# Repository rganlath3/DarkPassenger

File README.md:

# Dark Passenger

A modular payload for use as a ROS learning platform. Each floor of the chassis delivers different capabilities. The initial design is mounted on a differential drive roomba with plans to expand to treaded or quad-coptor platforms.

<!-- ABOUT THE PROJECT -->
## About The Project
The idea was to reuse a cheap roomba to create a platform for learning ROS2 and sensor integration. The end goal is to have a project incorporate aluminum extrusion chassis, working with acrylic, ESP32-S3, KiCAD PCB Development, stepper motors, thermal camera, depth camera, LIDAR, slip rings, DC motor controllers, encoders, 3D printing, INS sensor fusion, relays, GPS, SLAM, NAV2 (navigation stack) and power distribution.

### Design Tools & Requirements

#### Software Requirements
- VS Code (Programming IDE)
- Autodesk Fusion360 (Free CAD Software)
- KiCAD 9.0 (Open Source PCB Design Software)
- Ultimaker Cura (Free 3D Slicing Software)

#### Hardware Requirements
- Raspberry Pi 5
- 32GB+ SD Card
- 1x Dewalt 20VDC 2Ah Battery

## Hardware Development

### Bill of Materials
Coming Soon

### Hardware Used
#### Chassis
* 2020 T Slot Aluminum Extrusion
* 2020 2-Way Corner Brackets
* 2020 3-Way Corner Brackets
* M5 T Nuts and Screws
* 8x10 Black Translucent Acrylic Sheets 1/8" thick.

#### Floor 1
* 2x DROK Step Down Voltage Regulator
* 2x 3V Relay Modules
* 1x Custom Power Distribution PCB
* 1x Custom ESP3 GPIO PCB
* 1x ESP32-S3-N8R2
* 1x COB LED Strip Yellow
* 1x COB LED Strip Red
* 1x Cytron Dual Channel 10A DC Motor Driver
* 1x Quick Disconnect 12Pin Connector
* 1x MPU9250 IMU
* 1x GY-NEO6MV2 GPS Module

#### Floor 2
* 2x Acer USB Powered Hub
* 1x Raspberry Pi 5 (SBC)
* 1x Respeaker Microphone Array
* 1x ZED Stereo Labs Depth Camera

#### Floor 3
* 1x A1M8 RPLIDAR LIDAR Sensor
* 1x GPS Antenna

#### Floor 4
* 1x Custom ESP3 GPIO PCB
* 1x ESP32-S3-N8R2
* 1x Taidacent Hollow Slip Ring (Maybe 2x)
* 1x 5mm Flange Coupler
* 2x TMC2209 V1.3 Stepper Motor Driver
* 2x NEMA 17 Stepper (2A, 59Ncm), 48mm
* 1x Chameleon Camera Teledyne CM3-U3-13S2C-CS
* 3x 3V Relay Modules
* 1x MDD3A Dual Channel 3A DC Motor Driver
* 1x NERF Gun Gearbox
* 1x Laser Diode, 5V 1mA
* 1x COB LED Strip Yellow
* 1x 5V or 12V Cooling Fan

#### Misc
* Various Capacitors, Resistors, SMD LEDs, JST Connectors, Wire Crimps, etc.
* Various stranded wire lengths and colors: 16AWG, 22AWG.
* 1x 2.1mm DC Barrel Jacks Pair (Power Input)
* 1x SPST 20A Heavy Duty Toggle Switch (Projector Power and Pi Power)
* 2x SPST 5A Mini Toggle Switch (LED Power)
* 3D Printer: Creality CR-10SProV2

### Internal Block Diagram

### Electrical Interconnect Diagram
[Electrical Interconnect Diagram](/Hardware_Development/DrawIO/DarkPassengerElectricalInterconnect.pdf)

### PCBs
#### Power Distribution PCB

This PCB is used to stack 2x DC-DC converters below and a voltage cutoff board on the top. This PCB distributes power from battery inputs to get converted to 12V and 5V. It interfaces with the following components:

- Up to 2x 2Ah Dewalt Batteries
- Voltage Cutoff CCA (TBD)
- 20VDC to 5VDC Converter (TBD)
- 20VDC to 12VDC Converter (TBD)
- 3x Powered USB Ports
- Spare I2C

#### Base MCU PCB

This PCB is used to interface an ESP32-S3 with the following components:

- GPS Module (GY-NEO6mV2)
- MPU9250 IMU
- Spare I2C
- 2x Toggle Switches
- Neopixel Strip
- 2x Spare GPIOs
- External Reset
- 2x Channel Motor Driver (MDD10A)
- Battery Scaled Input
- Motor Encoders
- FWD LED Relay
- AFT LED Relay
- 5V Distribution

#### Turret MCU PCB

This PCB is used to interface an ESP32-S3 with the following components:

- GPS Module (GY-NEO6mV2)
- MPU9250 IMU
- Spare I2C
- Neopixel Strip
- External Reset
- 2x Channel Motor Driver (MDD3A)
- 2x NEMA17 Stepper Motors
- 2x TMC2209 Stepper Driver
- Laser Relay
- Turret LED Relay
- Cooling Fan Relay
- 5V Distribution
- 12V Distribution

### Power Budget and Power Draw
TBD

## Software Development
TBD
<!-- GETTING STARTED -->
## Getting Started

TBD
### Prerequisites
TBD

### Installation

TBD

### Common Issues

TBD

## Assets

TBD

<!-- ROADMAP -->
## Roadmap
- [] TBD

<p align="right">(<a href="#readme-top">back to top</a>)</p>

<!-- CONTRIBUTING -->
## Contributing & Donations

Any donation helps to support parts for future open source projects!
[Buy Me a Coffee ☕](https://www.buymeacoffee.com/rganlath)

Contributions are what make the open source community such an amazing place to learn, inspire, and create. Any contributions you make are **greatly appreciated**.

If you have a suggestion that would make this better, please fork the repo and create a pull request. You can also simply open an issue with the tag "enhancement".
Don't forget to give the project a star! Thanks again!

<p align="right">(<a href="#readme-top">back to top</a>)</p>

<!-- LICENSE -->
## License
The contents of this project itself is licensed under CERN-OHL-S-2.0 and the underlying source code is licensed under GNU GPLv3. Both of these licenses require attribution.

<p align="right">(<a href="#readme-top">back to top</a>)</p>

<!-- CONTACT -->
## Contact

Ranil Ganlath - ranil.ganlath@gmail.com

Project Link: TBD

<p align="right">(<a href="#readme-top">back to top</a>)</p>

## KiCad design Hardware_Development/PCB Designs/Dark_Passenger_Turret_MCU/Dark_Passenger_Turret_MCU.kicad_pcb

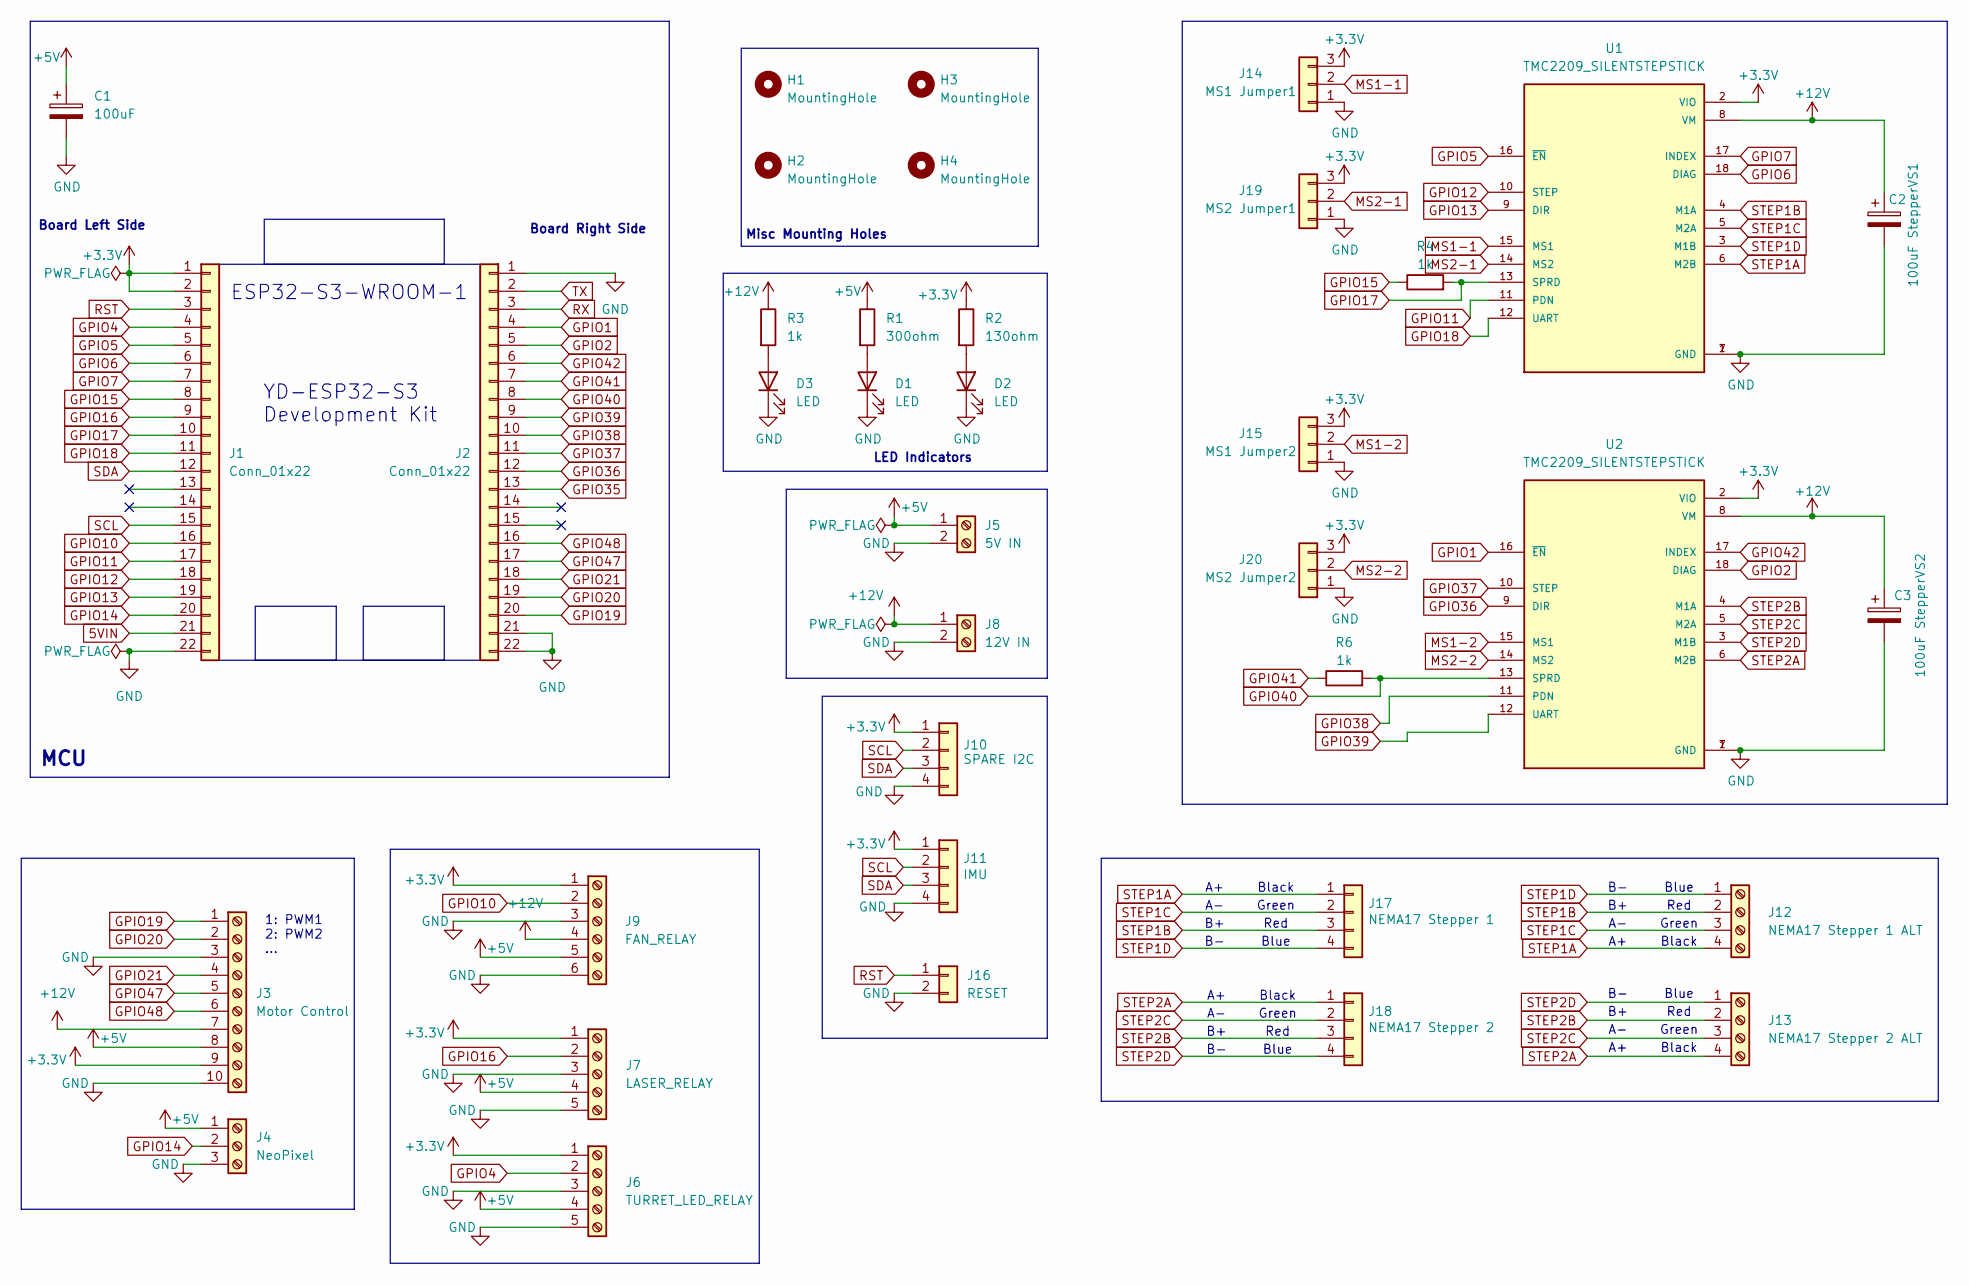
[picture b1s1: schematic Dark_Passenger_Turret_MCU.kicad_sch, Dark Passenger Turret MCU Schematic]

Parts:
C1: 100uF; CP_Radial_D10.0mm_P5.00mm
C2: 100uF StepperVS1; CP_Radial_D8.0mm_P5.00mm
C3: 100uF StepperVS2; CP_Radial_D8.0mm_P5.00mm
D1, D2, D3: LED; LED_1206_3216Metric_Pad1.42x1.75mm_HandSolder
H1, H2, H3, H4: MountingHole; MountingHole_3mm
J1, J2: Conn_01x22; PinSocket_1x22_P2.54mm_Vertical
J3: Motor Control; TerminalBlock_Phoenix_MPT-0,5-10-2.54_1x10_P2.54mm_Horizont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
J4: NeoPixel; TerminalBlock_Phoenix_MPT-0,5-3-2.54_1x03_P2.54mm_Horizontal
J5: 5V IN; TerminalBlock_Phoenix_MKDS-1,5-2_1x02_P5.00mm_Horizontal
J6: TURRET_LED_RELAY; TerminalBlock_Phoenix_MPT-0,5-5-2.54_1x05_P2.54mm_Horizontal
J7: LASER_RELAY; TerminalBlock_Phoenix_MPT-0,5-5-2.54_1x05_P2.54mm_Horizontal
J8: 12V IN; TerminalBlock_Phoenix_MKDS-1,5-2_1x02_P5.00mm_Horizontal
J9: FAN_RELAY; TerminalBlock_Phoenix_MPT-0,5-6-2.54_1x06_P2.54mm_Horizontal
J10: SPARE I2C; PinSocket_1x04_P2.54mm_Vertical
J11: IMU; PinSocket_1x04_P2.54mm_Vertical
J12: NEMA17 Stepper 1 ALT; TerminalBlock_Phoenix_MPT-0,5-4-2.54_1x04_P2.54mm_Horizontal
J13: NEMA17 Stepper 2 ALT; TerminalBlock_Phoenix_MPT-0,5-4-2.54_1x04_P2.54mm_Horizontal
J14: MS1 Jumper1; PinHeader_1x03_P2.54mm_Vertical
J15: MS1 Jumper2; PinHeader_1x03_P2.54mm_Vertical
J16: RESET; PinSocket_1x02_P2.54mm_Vertical
J17: NEMA17 Stepper 1; PinSocket_1x04_P2.54mm_Vertical
J18: NEMA17 Stepper 2; PinSocket_1x04_P2.54mm_Vertical
J19: MS2 Jumper1; PinHeader_1x03_P2.54mm_Vertical
J20: MS2 Jumper2; PinHeader_1x03_P2.54mm_Vertical
R1: 300ohm; R_1206_3216Metric_Pad1.30x1.75mm_HandSolder
R2: 130ohm; R_1206_3216Metric_Pad1.30x1.75mm_HandSolder
R3, R4, R6: 1k; R_1206_3216Metric_Pad1.30x1.75mm_HandSolder
U1, U2: TMC2209_SILENTSTEPSTICK; MODULE_TMC2209_SILENTSTEPSTICK; PARTREV 1.20

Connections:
5VIN: J1.21
+3.3V: J1.1, J1.2, J3.9, J6.1, J7.1, J9.1, J10.1, J11.1, J14.3, J15.3, J19.3, J20.3, R2.1, U1.2 (VIO), U2.2 (VIO)
+5V: C1.1, J3.8, J4.1, J5.1, J6.4, J7.4, J9.5, R1.1
+12V: C2.1, C3.1, J3.7, J8.1, J9.4, R3.1, U1.8 (VM), U2.8 (VM)
GND: C1.2, C2.2, C3.2, D1.1 (K), D2.1 (K), D3.1 (K), J1.22, J2.1, J2.21, J2.22, J3.3, J3.10, J4.3, J5.2, J6.3, J6.5, J7.3, J7.5, J8.2, J9.3, J9.6, J10.4, J11.4, J14.1, J15.1, J16.2, J19.1, J20.1, U1.1 (GND), U1.7 (GND), U2.1 (GND), U2.7 (GND)
GPIO1: J2.4, U2.16 (~EN)
GPIO2: J2.5, U2.18 (DIAG)
GPIO4: J1.4, J6.2
GPIO5: J1.5, U1.16 (~EN)
GPIO6: J1.6, U1.18 (DIAG)
GPIO7: J1.7, U1.17 (INDEX)
GPIO10: J1.16, J9.2
GPIO11: J1.17, U1.11 (PDN)
GPIO12: J1.18, U1.10 (STEP)
GPIO13: J1.19, U1.9 (DIR)
GPIO14: J1.20, J4.2
GPIO15: J1.8, R4.1
GPIO16: J1.9, J7.2
GPIO17: J1.10, R4.2, U1.13 (SPRD)
GPIO18: J1.11, U1.12 (UART)
GPIO19: J2.20, J3.1
GPIO20: J2.19, J3.2
GPIO21: J2.18, J3.4
GPIO35: J2.13
GPIO36: J2.12, U2.9 (DIR)
GPIO37: J2.11, U2.10 (STEP)
GPIO38: J2.10, U2.11 (PDN)
GPIO39: J2.9, U2.12 (UART)
GPIO40: J2.8, R6.2, U2.13 (SPRD)
GPIO41: J2.7, R6.1
GPIO42: J2.6, U2.17 (INDEX)
GPIO47: J2.17, J3.5
GPIO48: J2.16, J3.6
MS1-1: J14.2, U1.15 (MS1)
MS1-2: J15.2, U2.15 (MS1)
MS2-1: J19.2, U1.14 (MS2)
MS2-2: J20.2, U2.14 (MS2)
unnamed: D1.2 (A), R1.2
unnamed: D2.2 (A), R2.2
unnamed: D3.2 (A), R3.2
RST: J1.3, J16.1
RX: J2.3
SCL: J1.15, J10.2, J11.2
SDA: J1.12, J10.3, J11.3
STEP1A: J12.4, J17.1, U1.6 (M2B)
STEP1B: J12.2, J17.3, U1.4 (M1A)
STEP1C: J12.3, J17.2, U1.5 (M2A)
STEP1D: J12.1, J17.4, U1.3 (M1B)
STEP2A: J13.4, J18.1, U2.6 (M2B)
STEP2B: J13.2, J18.3, U2.4 (M1A)
STEP2C: J13.3, J18.2, U2.5 (M2A)
STEP2D: J13.1, J18.4, U2.3 (M1B)
TX: J2.2

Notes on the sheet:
Red
Blue
Misc Mounting Holes
ESP32-S3-WROOM-1
Black
Board Right Side
MCU
LED Indicators
Green
Board Left Side
1: PWM1 2: PWM2 ...
YD-ESP32-S3 Development Kit

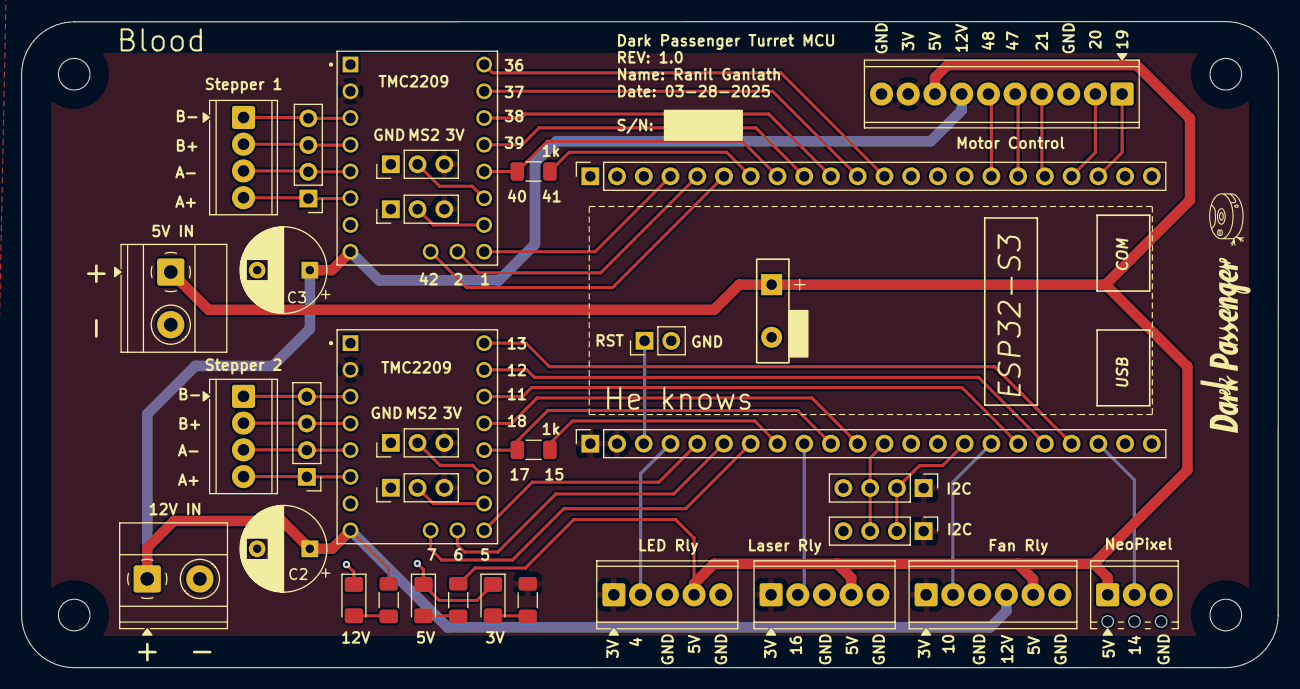
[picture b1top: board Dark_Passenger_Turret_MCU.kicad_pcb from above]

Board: 2 copper layers, 119.4 x 61.4 mm, 37 parts (0 on the bottom side), 49 nets.

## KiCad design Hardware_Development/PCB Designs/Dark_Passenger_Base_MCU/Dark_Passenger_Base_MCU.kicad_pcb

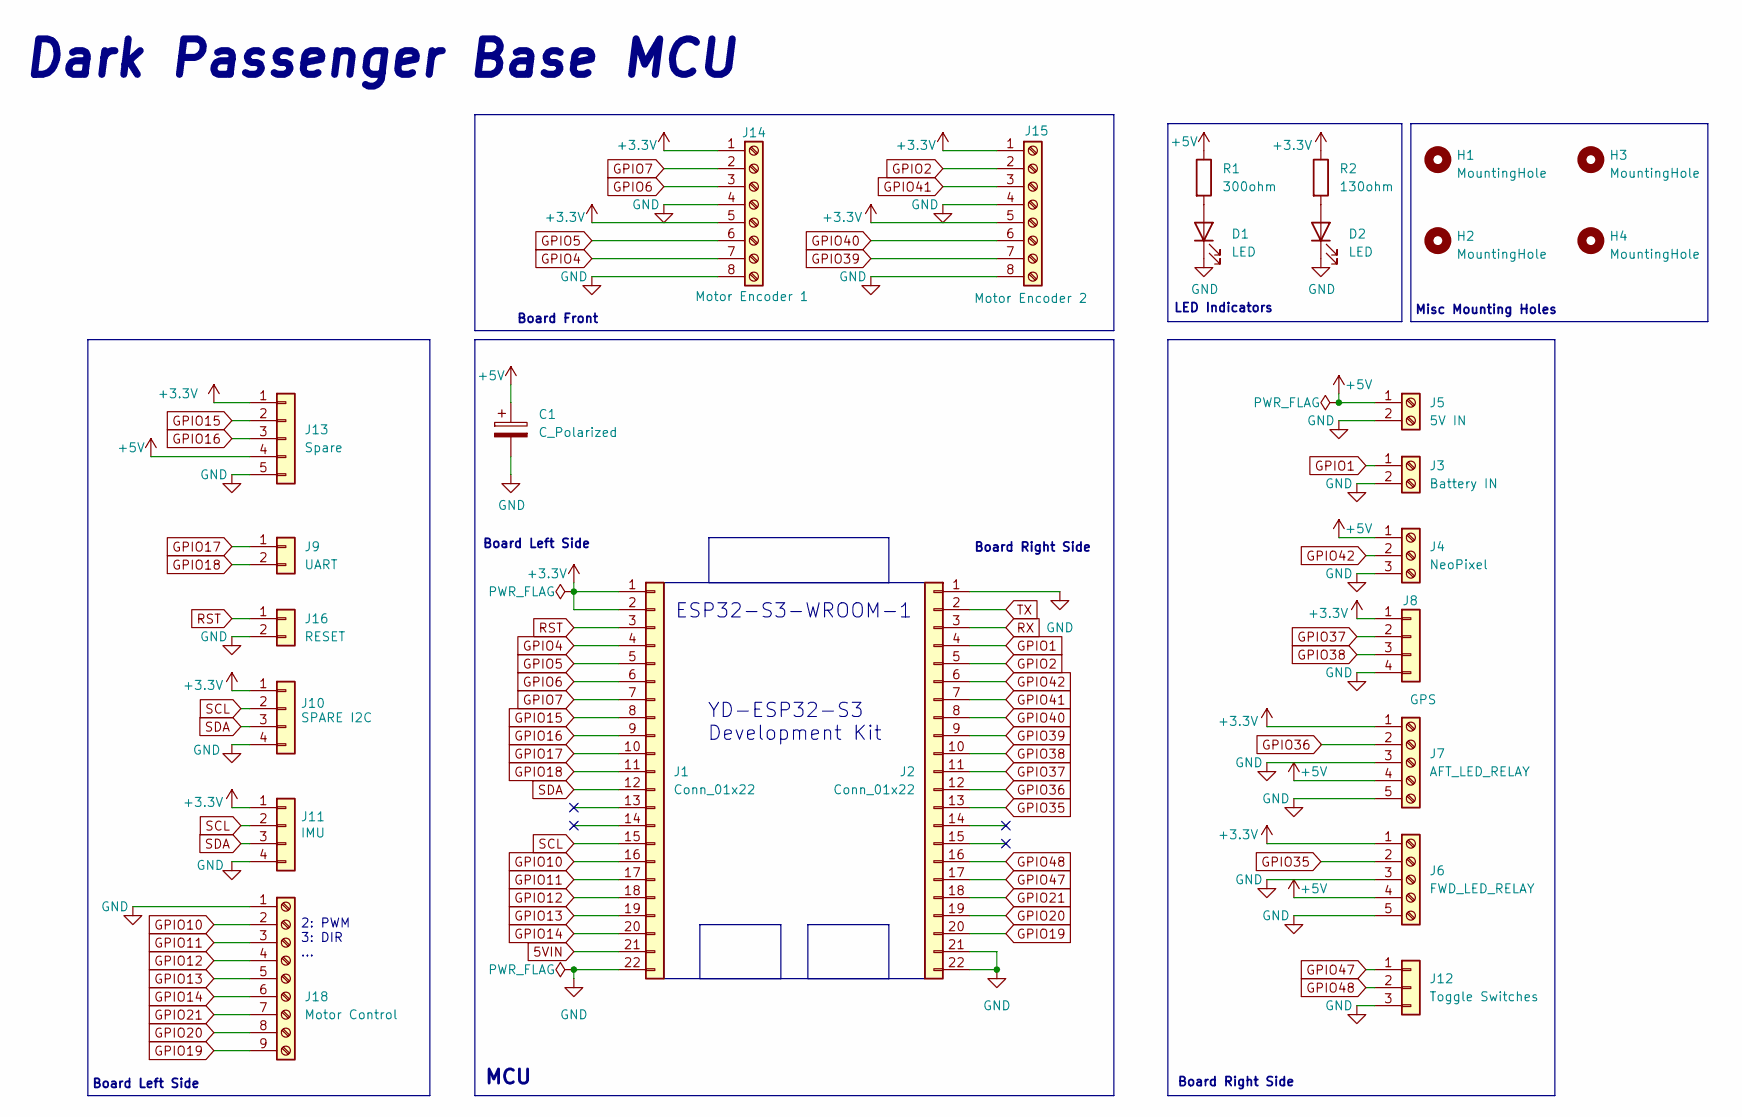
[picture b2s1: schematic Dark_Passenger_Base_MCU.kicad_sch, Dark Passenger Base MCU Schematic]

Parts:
C1: C_Polarized; CP_Radial_D10.0mm_P5.00mm
D1, D2: LED; LED_1206_3216Metric_Pad1.42x1.75mm_HandSolder
H1, H2, H3, H4: MountingHole; MountingHole_3mm
J1, J2: Conn_01x22; PinSocket_1x22_P2.54mm_Vertical
J3: Battery IN; TerminalBlock_Phoenix_MPT-0,5-2-2.54_1x02_P2.54mm_Horizontal
J4: NeoPixel; TerminalBlock_Phoenix_MPT-0,5-3-2.54_1x03_P2.54mm_Horizontal
J5: 5V IN; TerminalBlock_Phoenix_MKDS-1,5-2_1x02_P5.00mm_Horizontal
J6: FWD_LED_RELAY; TerminalBlock_Phoenix_MPT-0,5-5-2.54_1x05_P2.54mm_Horizontal
J7: AFT_LED_RELAY; TerminalBlock_Phoenix_MPT-0,5-5-2.54_1x05_P2.54mm_Horizontal
J8: GPS; PinSocket_1x04_P2.54mm_Vertical
J9: UART; PinSocket_1x02_P2.54mm_Vertical
J10: SPARE I2C; PinSocket_1x04_P2.54mm_Vertical
J11: IMU; PinSocket_1x04_P2.54mm_Vertical
J12: Toggle Switches; PinSocket_1x03_P2.54mm_Vertical
J13: Spare; PinSocket_1x05_P2.54mm_Vertical
J14: Motor Encoder 1; TerminalBlock_Phoenix_MPT-0,5-8-2.54_1x08_P2.54mm_Horizontal
J15: Motor Encoder 2; TerminalBlock_Phoenix_MPT-0,5-8-2.54_1x08_P2.54mm_Horizontal
J16: RESET; PinSocket_1x02_P2.54mm_Vertical
J18: Motor Control; TerminalBlock_Phoenix_MPT-0,5-9-2.54_1x09_P2.54mm_Horizontal
R1: 300ohm; R_1206_3216Metric_Pad1.30x1.75mm_HandSolder
R2: 130ohm; R_1206_3216Metric_Pad1.30x1.75mm_HandSolder

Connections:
5VIN: J1.21
+3.3V: J1.1, J1.2, J6.1, J7.1, J8.1, J10.1, J11.1, J13.1, J14.1, J14.5, J15.1, J15.5, R2.1
+5V: C1.1, J4.1, J5.1, J6.4, J7.4, J13.4, R1.1
GND: C1.2, D1.1 (K), D2.1 (K), J1.22, J2.1, J2.21, J2.22, J3.2, J4.3, J5.2, J6.3, J6.5, J7.3, J7.5, J8.4, J10.4, J11.4, J12.3, J13.5, J14.4, J14.8, J15.4, J15.8, J16.2, J18.1
GPIO1: J2.4, J3.1
GPIO2: J2.5, J15.2
GPIO4: J1.4, J14.7
GPIO5: J1.5, J14.6
GPIO6: J1.6, J14.3
GPIO7: J1.7, J14.2
GPIO10: J1.16, J18.2
GPIO11: J1.17, J18.3
GPIO12: J1.18, J18.4
GPIO13: J1.19, J18.5
GPIO14: J1.20, J18.6
GPIO15: J1.8, J13.2
GPIO16: J1.9, J13.3
GPIO17: J1.10, J9.1
GPIO18: J1.11, J9.2
GPIO19: J2.20, J18.9
GPIO20: J2.19, J18.8
GPIO21: J2.18, J18.7
GPIO35: J2.13, J6.2
GPIO36: J2.12, J7.2
GPIO37: J2.11, J8.2
GPIO38: J2.10, J8.3
GPIO39: J2.9, J15.7
GPIO40: J2.8, J15.6
GPIO41: J2.7, J15.3
GPIO42: J2.6, J4.2
GPIO47: J2.17, J12.1
GPIO48: J2.16, J12.2
unnamed: D1.2 (A), R1.2
unnamed: D2.2 (A), R2.2
RST: J1.3, J16.1
RX: J2.3
SCL: J1.15, J10.2, J11.2
SDA: J1.12, J10.3, J11.3
TX: J2.2

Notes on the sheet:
Board Right Side
Board Front
Misc Mounting Holes
ESP32-S3-WROOM-1
Board Left Side
MCU
Dark Passenger Base MCU
LED Indicators
2: PWM 3: DIR ...
YD-ESP32-S3 Development Kit

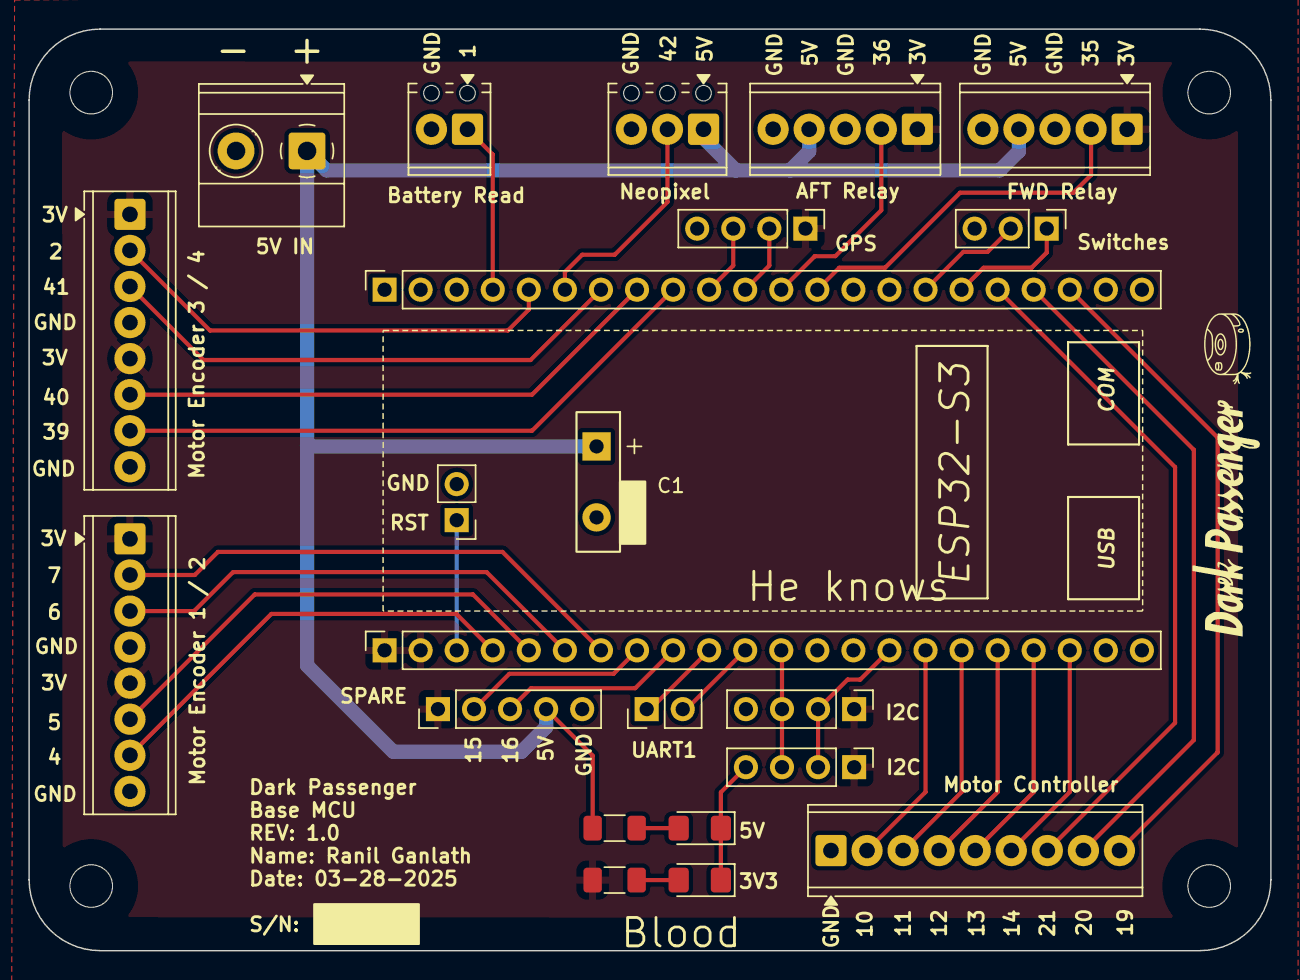
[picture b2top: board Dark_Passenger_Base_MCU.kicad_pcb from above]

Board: 2 copper layers, 87.5 x 64.9 mm, 26 parts (0 on the bottom side), 36 nets.

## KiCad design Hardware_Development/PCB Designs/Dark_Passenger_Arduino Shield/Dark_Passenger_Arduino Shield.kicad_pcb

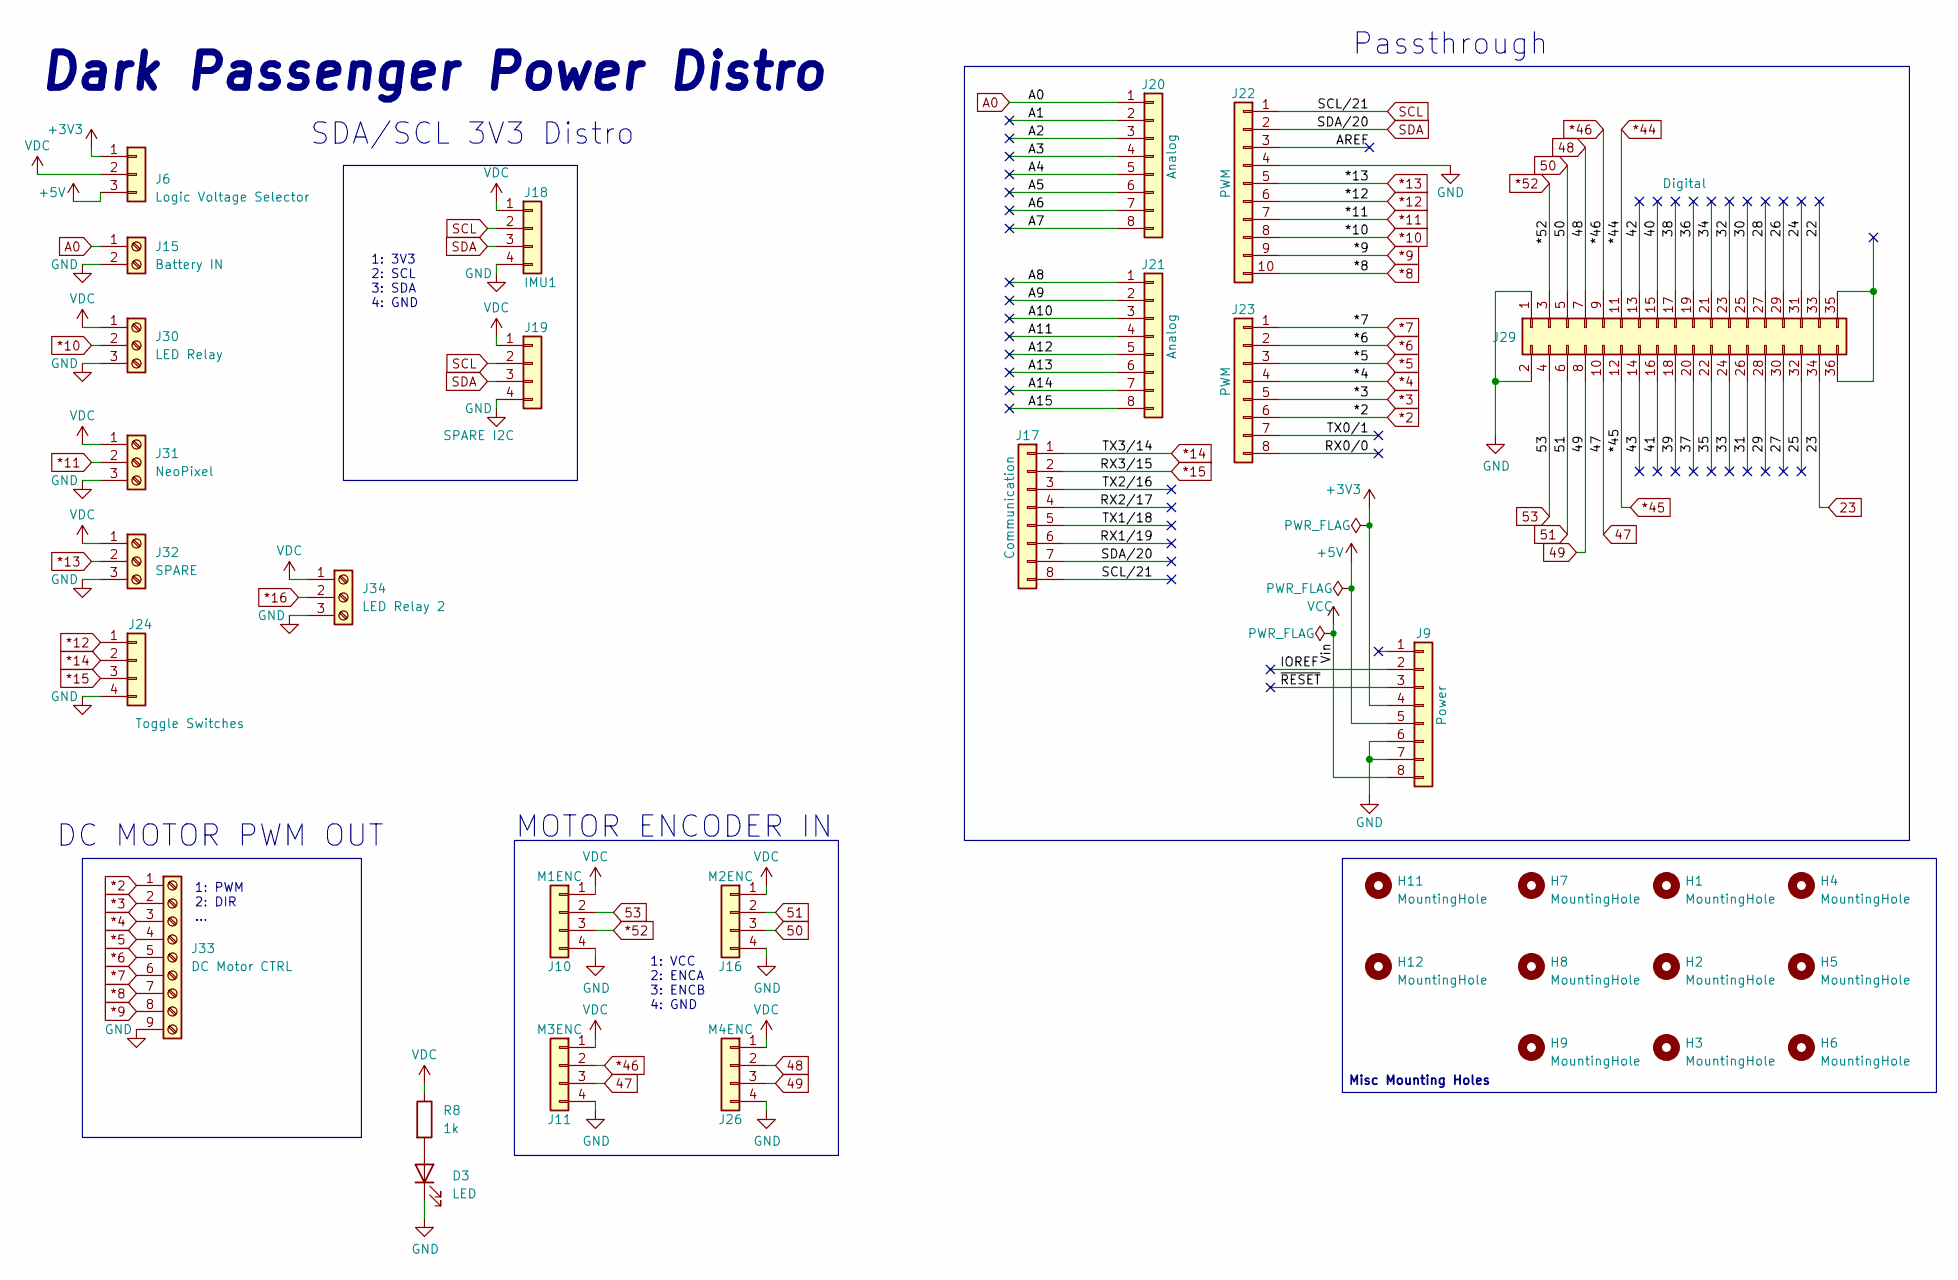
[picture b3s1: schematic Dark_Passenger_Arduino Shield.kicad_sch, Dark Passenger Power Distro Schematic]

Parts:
D3: LED; LED_1206_3216Metric_Pad1.42x1.75mm_HandSolder
H1, H2, H3, H4, H5, H6, H7, H8, H9, H11, H12: MountingHole; MountingHole_3mm
J6: Logic Voltage Selector; PinSocket_1x03_P2.54mm_Vertical
J9: Power; PinSocket_1x08_P2.54mm_Vertical
J10: M1ENC; PinSocket_1x04_P2.54mm_Vertical
J11: M3ENC; PinSocket_1x04_P2.54mm_Vertical
J15: Battery IN; TerminalBlock_Phoenix_MPT-0,5-2-2.54_1x02_P2.54mm_Horizontal
J16: M2ENC; PinSocket_1x04_P2.54mm_Vertical
J17: Communication; PinSocket_1x08_P2.54mm_Vertical
J18: IMU1; PinSocket_1x04_P2.54mm_Vertical
J19: SPARE I2C; PinSocket_1x04_P2.54mm_Vertical
J20, J21: Analog; PinSocket_1x08_P2.54mm_Vertical
J22: PWM; PinSocket_1x10_P2.54mm_Vertical
J23: PWM; PinSocket_1x08_P2.54mm_Vertical
J24: Toggle Switches; PinSocket_1x04_P2.54mm_Vertical
J26: M4ENC; PinSocket_1x04_P2.54mm_Vertical
J29: Digital; PinSocket_2x18_P2.54mm_Vertical
J30: LED Relay; TerminalBlock_Phoenix_MPT-0,5-3-2.54_1x03_P2.54mm_Horizontal
J31: NeoPixel; TerminalBlock_Phoenix_MPT-0,5-3-2.54_1x03_P2.54mm_Horizontal
J32: SPARE; TerminalBlock_Phoenix_MPT-0,5-3-2.54_1x03_P2.54mm_Horizontal
J33: DC Motor CTRL; TerminalBlock_Phoenix_MPT-0,5-9-2.54_1x09_P2.54mm_Horizontal
J34: LED Relay 2; TerminalBlock_Phoenix_MPT-0,5-3-2.54_1x03_P2.54mm_Horizontal
R8: 1k; R_1206_3216Metric_Pad1.30x1.75mm_HandSolder

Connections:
23: J29.34
47: J11.3, J29.10
48: J26.2, J29.7
49: J26.3, J29.8
50: J16.3, J29.5
51: J16.2, J29.6
53: J10.2, J29.4
*2: J23.6, J33.1
*3: J23.5, J33.2
*4: J23.4, J33.3
*5: J23.3, J33.4
*6: J23.2, J33.5
*7: J23.1, J33.6
*8: J22.10, J33.7
*9: J22.9, J33.8
*10: J22.8, J30.2
*11: J22.7, J31.2
*12: J22.6, J24.1
*13: J22.5, J32.2
*14: J17.1, J24.2
*15: J17.2, J24.3
*16: J34.2
*44: J29.11
*45: J29.12
*46: J11.2, J29.9
*52: J10.3, J29.3
+3V3: J6.1, J9.4
+5V: J6.3, J9.5
/22: J29.33
/24: J29.31
/25: J29.32
/26: J29.29
/27: J29.30
/28: J29.27
/29: J29.28
/30: J29.25
/31: J29.26
/32: J29.23
/33: J29.24
/34: J29.21
/35: J29.22
/36: J29.19
/37: J29.20
/38: J29.17
/39: J29.18
/40: J29.15
/41: J29.16
/42: J29.13
/43: J29.14
/A1: J20.2
/A2: J20.3
/A3: J20.4
/A4: J20.5
/A5: J20.6
/A6: J20.7
/A7: J20.8
/A8: J21.1
/A9: J21.2
/A10: J21.3
/A11: J21.4
/A12: J21.5
/A13: J21.6
/A14: J21.7
/A15: J21.8
/AREF: J22.3
/IOREF: J9.2
/RX0/0: J23.8
/RX1/19: J17.6
/RX2/17: J17.4
/TX0/1: J23.7
/TX1/18: J17.5
/TX2/16: J17.3
/~RESET: J9.3
A0: J15.1, J20.1
GND: D3.1 (K), J9.6, J9.7, J10.4, J11.4, J15.2, J16.4, J18.4, J19.4, J22.4, J24.4, J26.4, J29.1, J29.2, J30.3, J31.3, J32.3, J33.9, J34.3
unnamed: D3.2 (A), R8.2
SCL: J17.8, J18.2, J19.2, J22.1
SDA: J17.7, J18.3, J19.3, J22.2
VCC: J9.8
VDC: J6.2, J10.1, J11.1, J16.1, J18.1, J19.1, J26.1, J30.1, J31.1, J32.1, J34.1, R8.1

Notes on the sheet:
Misc Mounting Holes
DC MOTOR PWM OUT
Dark Passenger Power Distro
MOTOR ENCODER IN
SDA/SCL 3V3 Distro
1: 3V3 2: SCL 3: SDA 4: GND
1: PWM 2: DIR ...
1: VCC 2: ENCA 3: ENCB 4: GND
Passthrough

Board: 2 copper layers, 37 parts (0 on the bottom side), 30 nets, no tracks yet.

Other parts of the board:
MH1, MH5, MH6: MountingHole_3.2mm

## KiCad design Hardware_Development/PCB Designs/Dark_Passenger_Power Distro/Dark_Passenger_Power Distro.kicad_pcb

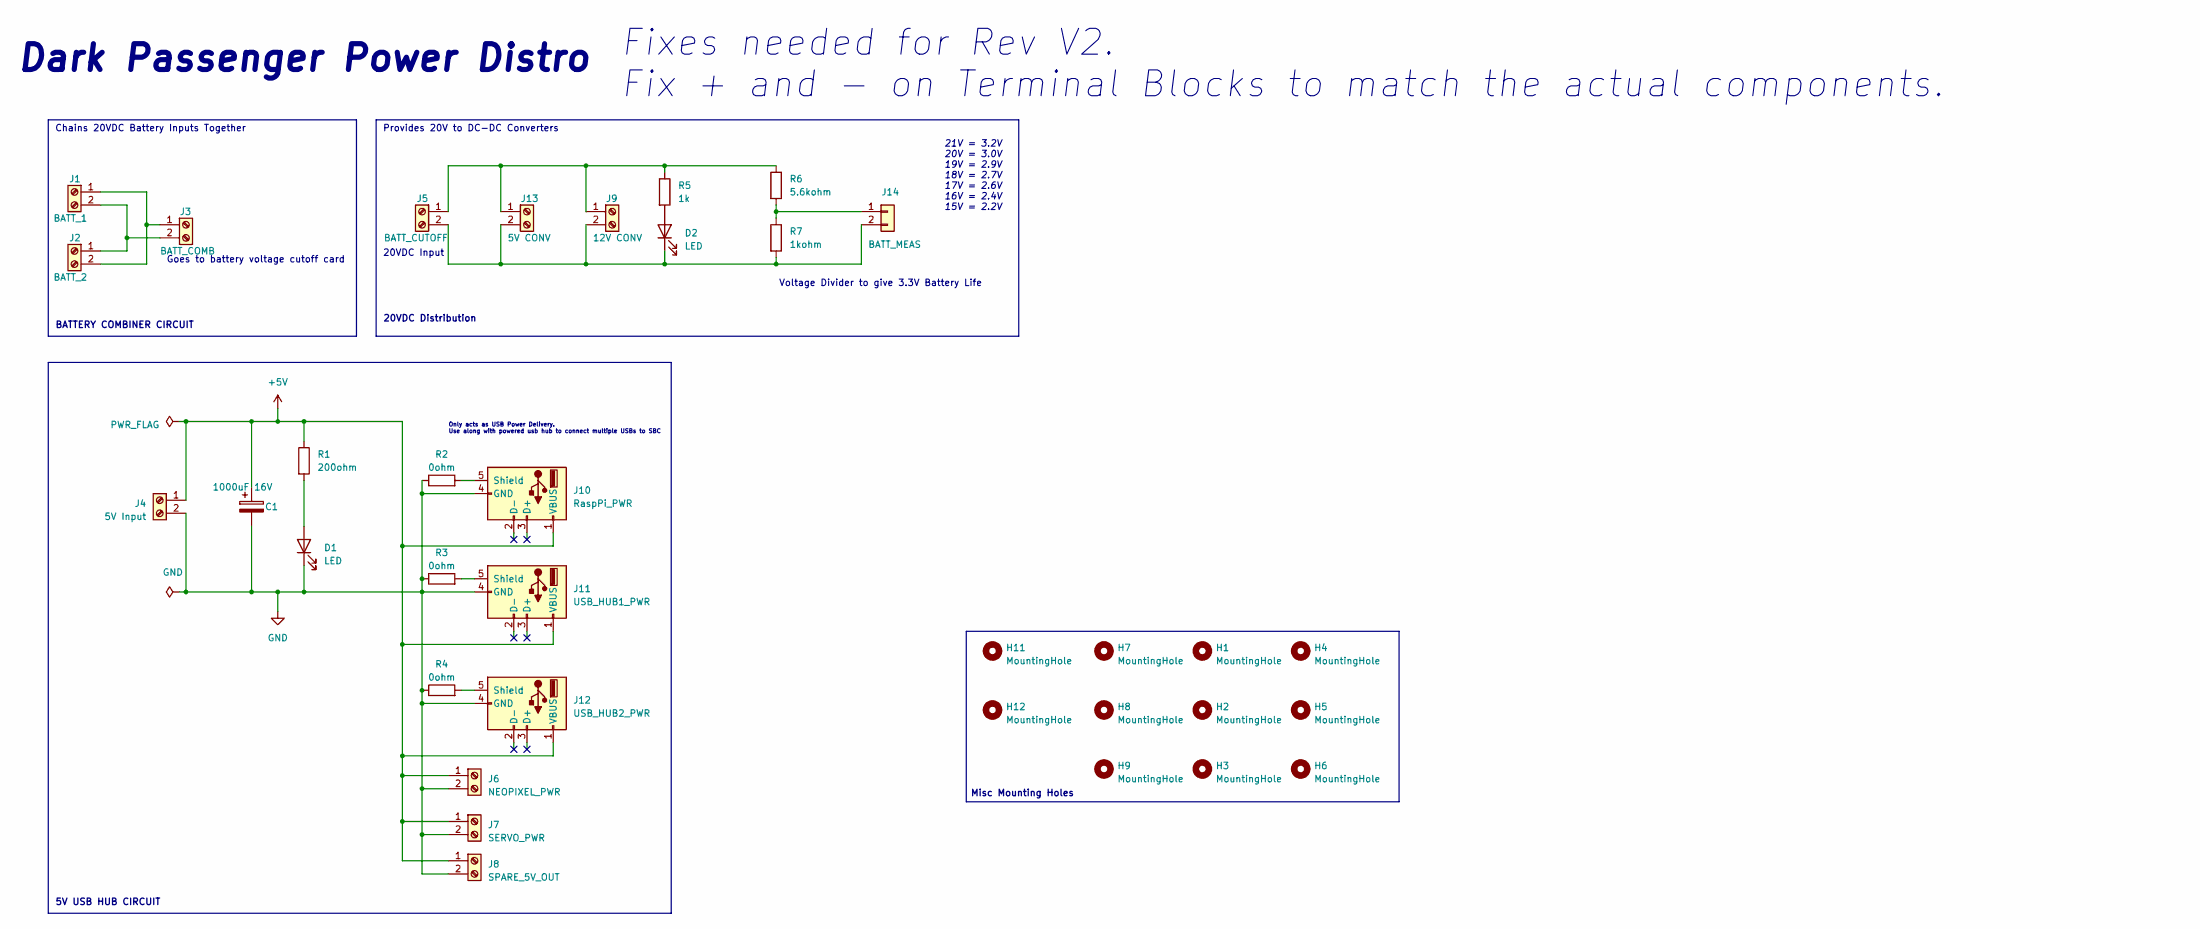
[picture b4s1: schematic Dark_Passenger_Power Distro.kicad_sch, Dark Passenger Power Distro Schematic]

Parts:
C1: 1000uF 16V; C_Radial_D10.0mm_H16.0mm_P5.00mm
D1, D2: LED; LED_1206_3216Metric_Pad1.42x1.75mm_HandSolder
H1, H2, H3, H4, H5, H6, H7, H8, H9, H11, H12: MountingHole; MountingHole_3mm
J1: BATT_1; TerminalBlock_Phoenix_MKDS-1,5-2_1x02_P5.00mm_Horizontal
J2: BATT_2; TerminalBlock_Phoenix_MKDS-1,5-2_1x02_P5.00mm_Horizontal
J3: BATT_COMB; TerminalBlock_Phoenix_MKDS-1,5-2_1x02_P5.00mm_Horizontal
J4: 5V Input; TerminalBlock_Phoenix_MKDS-1,5-2_1x02_P5.00mm_Horizontal
J5: BATT_CUTOFF; TerminalBlock_Phoenix_MKDS-1,5-2_1x02_P5.00mm_Horizontal
J6: NEOPIXEL_PWR; TerminalBlock_Phoenix_MKDS-1,5-2_1x02_P5.00mm_Horizontal
J7: SERVO_PWR; TerminalBlock_Phoenix_MKDS-1,5-2_1x02_P5.00mm_Horizontal
J8: SPARE_5V_OUT; TerminalBlock_Phoenix_MKDS-1,5-2_1x02_P5.00mm_Horizontal
J9: 12V CONV; TerminalBlock_Phoenix_MKDS-1,5-2_1x02_P5.00mm_Horizontal
J10: RaspPi_PWR; USB_A_Molex_67643_Horizontal
J11: USB_HUB1_PWR; USB_A_Molex_67643_Horizontal
J12: USB_HUB2_PWR; USB_A_Molex_67643_Horizontal
J13: 5V CONV; TerminalBlock_Phoenix_MKDS-1,5-2_1x02_P5.00mm_Horizontal
J14: BATT_MEAS; PinHeader_1x02_P2.54mm_Vertical
R1: 200ohm; R_1206_3216Metric_Pad1.30x1.75mm_HandSolder
R2, R3, R4: 0ohm; R_1206_3216Metric_Pad1.30x1.75mm_HandSolder
R5: 1k; R_1206_3216Metric_Pad1.30x1.75mm_HandSolder
R6: 5.6kohm; R_1206_3216Metric_Pad1.30x1.75mm_HandSolder
R7: 1kohm; R_1206_3216Metric_Pad1.30x1.75mm_HandSolder

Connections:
+5V: C1.1, J4.1, J6.1, J7.1, J8.1, J10.1 (VBUS), J11.1 (VBUS), J12.1 (VBUS), R1.1
GND: C1.2, D1.1 (K), J4.2, J6.2, J7.2, J8.2, J10.4 (GND), J11.4 (GND), J12.4 (GND), R2.1, R3.1, R4.1
unnamed: D1.2 (A), R1.2
unnamed: D2.2 (A), R5.2
unnamed: D2.1 (K), J5.2, J9.2, J13.2, J14.2, R7.2
unnamed: J1.1, J2.2, J3.1
unnamed: J1.2, J2.1, J3.2
unnamed: J10.5 (Shield), R2.2
unnamed: J11.5 (Shield), R3.2
unnamed: J12.5 (Shield), R4.2
unnamed: J5.1, J9.1, J13.1, R5.1, R6.1
unnamed: J14.1, R6.2, R7.1

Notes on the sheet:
Fixes needed for Rev V2. Fix + and - on Terminal Blocks to match the actual components.
20VDC Distribution
5V USB HUB CIRCUIT
Misc Mounting Holes
21V = 3.2V 20V = 3.0V 19V = 2.9V 18V = 2.7V 17V = 2.6V 16V = 2.4V 15V = 2.2V
Voltage Divider to give 3.3V Battery Life
20VDC Input
Dark Passenger Power Distro
Chains 20VDC Battery Inputs Together
Only acts as USB Power Delivery. Use along with powered usb hub to connect multiple USBs to SBC
Goes to battery voltage cutoff card
BATTERY COMBINER CIRCUIT
Provides 20V to DC-DC Converters

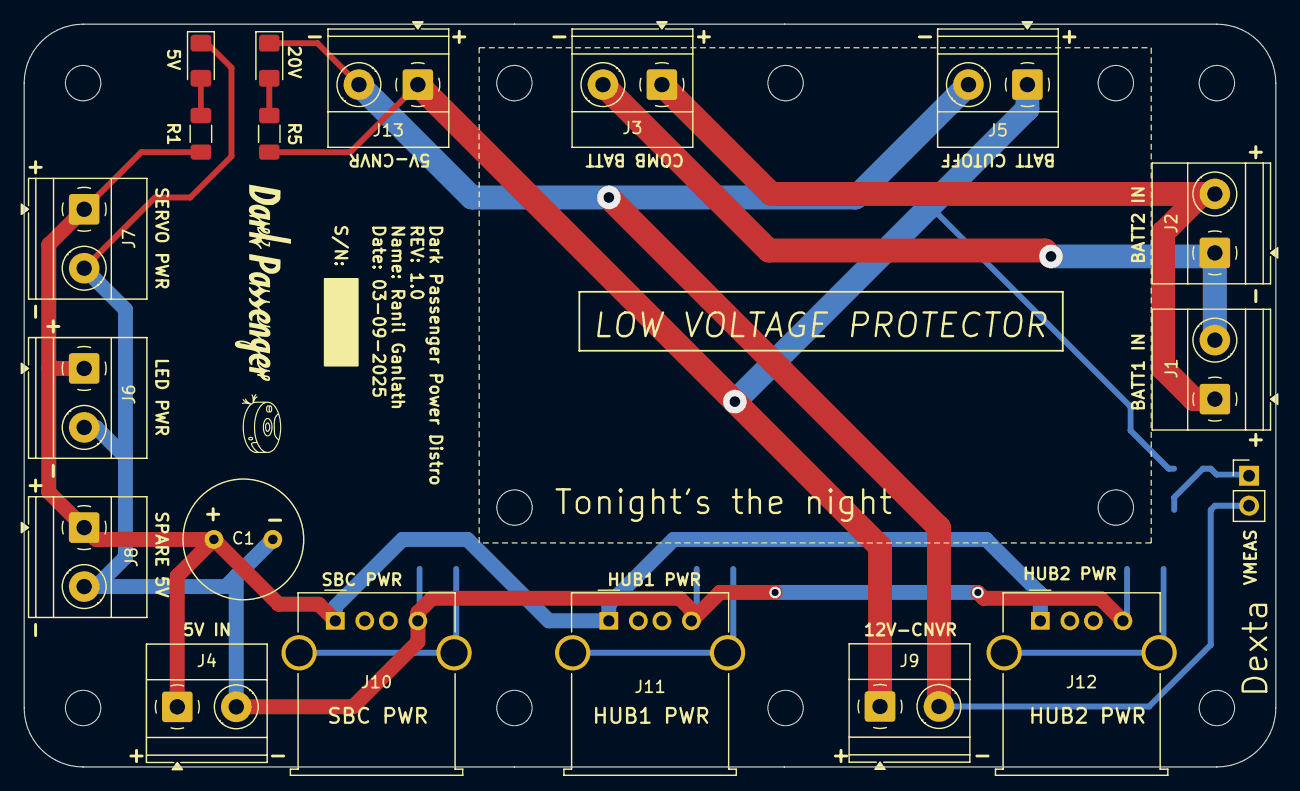
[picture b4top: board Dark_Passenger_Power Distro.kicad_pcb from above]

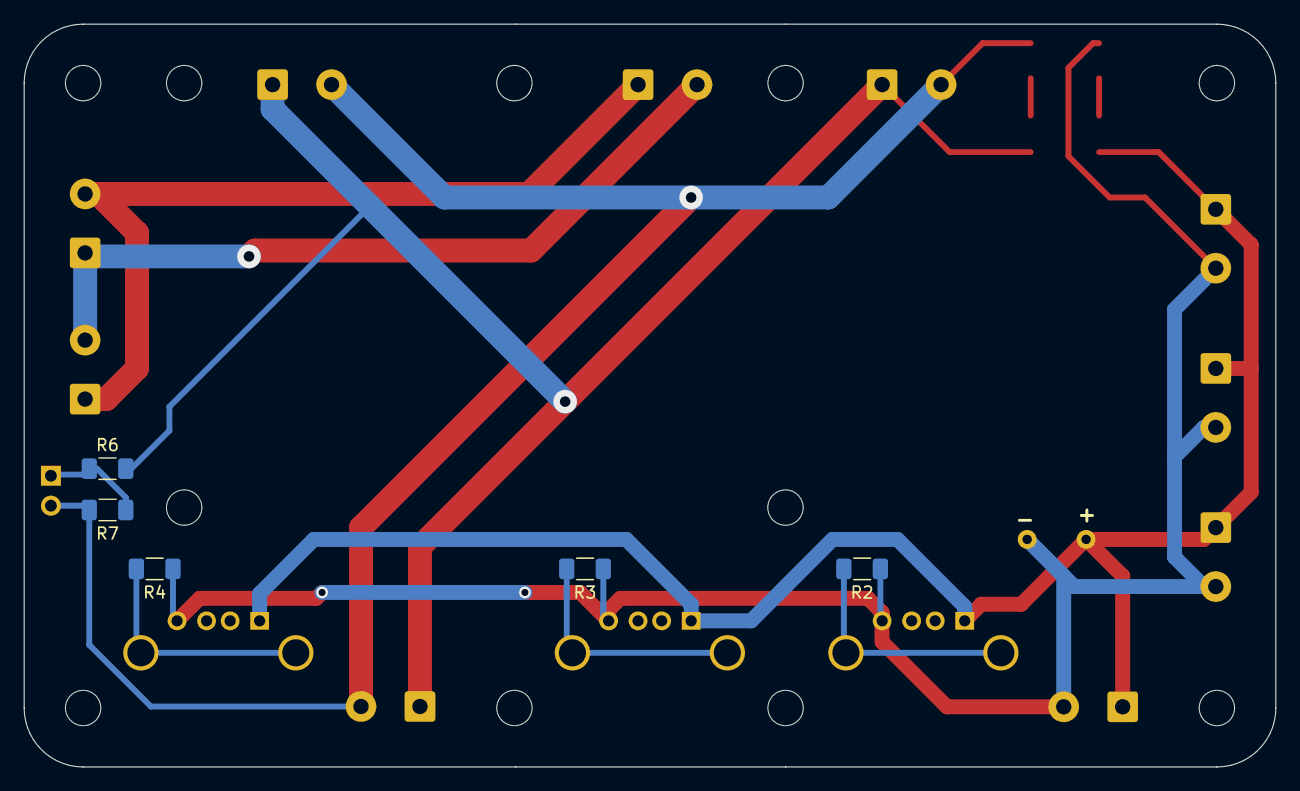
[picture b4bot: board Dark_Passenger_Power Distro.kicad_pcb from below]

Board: 2 copper layers, 106.2 x 63.0 mm, 35 parts (5 on the bottom side), 12 nets.

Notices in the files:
README.md:
Hardware License: CERN-OHL-S-2.0
Software License: GPL v3
